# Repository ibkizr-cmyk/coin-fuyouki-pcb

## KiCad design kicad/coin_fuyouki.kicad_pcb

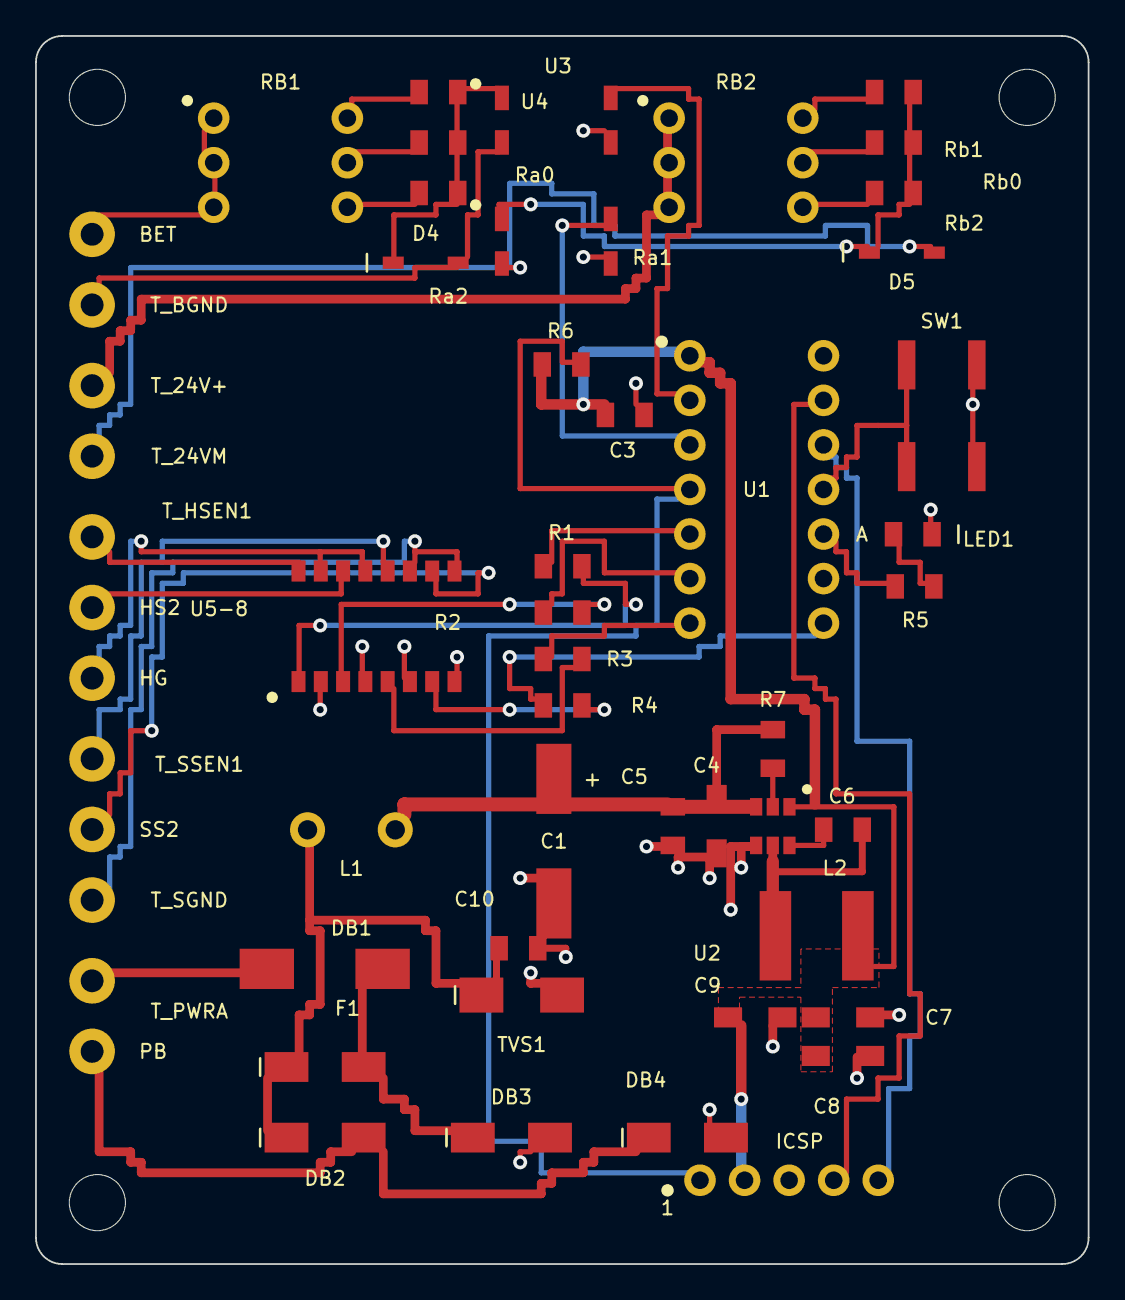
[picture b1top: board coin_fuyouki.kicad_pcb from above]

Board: 2 copper layers, 60.0 x 70.0 mm, 58 parts (0 on the bottom side), 44 nets.

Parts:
C1: EEE-FK1V101P; C1_custom
C3: 0.1uF; C3_custom
C4: 10uF/50V; C4_custom
C5: 0.1uF/50V; C5_custom
C6: 0.1uF; C6_custom
C7: 22uF/25V; C7_custom
C8: 22uF/25V; C8_custom
C9: 22uF/25V; C9_custom
C10: 0.1uF; C10_custom
D4: 1N4148W; D4_custom
D5: 1N4148W; D5_custom
DB1: SS16; DB1_custom
DB2: SS16; DB2_custom
DB3: SS16; DB3_custom
DB4: SS16; DB4_custom
F1: MF-SM050-2; F1_custom
H1, H2, H3, H4: M3; MountingHole_3.2mm
ICSP: 5P; ICSP_custom
L1: 100uH; L1_custom
L2: SRN6045TA-6R8M; L2_custom
LED1: LED; LED1_custom
R1: 470; R1_custom
R2: 470; R2_custom
R3: 470; R3_custom
R4: 470; R4_custom
R5: 1k; R5_custom
R6: 10k; R6_custom
R7: 100k; R7_custom
RB1: DIP3; RB1_custom
RB2: DIP3; RB2_custom
Ra0: 820; Ra0_custom
Ra1: 2.2k; Ra1_custom
Ra2: 4.7k; Ra2_custom
Rb0: 820; Rb0_custom
Rb1: 2.2k; Rb1_custom
Rb2: 4.7k; Rb2_custom
SW1: TACT; SW1_custom
TVS1: SMBJ26A; TVS1_custom
T_24V+: T_24V+_custom
T_24VM: T_24VM_custom
T_BET: T_BET_custom
T_BGND: T_BGND_custom
T_HGND: T_HGND_custom
T_HSEN1: T_HSEN1_custom
T_HSEN2: T_HSEN2_custom
T_PWRA: T_PWRA_custom
T_PWRB: T_PWRB_custom
T_SGND: T_SGND_custom
T_SSEN1: T_SSEN1_custom
T_SSEN2: T_SSEN2_custom
U1: PIC16F1503-I/P; U1_custom
U2: AP63205; U2_custom
U3: PC817; U3_custom
U4: PC817; U4_custom
U5-8: TLP291-4; U5-8_custom

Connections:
BA: D4.1, Ra0.2, Ra1.2, Ra2.2, U3.1
BET: RB1.1, RB1.2, RB1.3, T_BET.1
BETIN: U1.2, U3.4
BGND: D4.2, T_BGND.1, U3.2
BST: C6.1, U2.6
D1_a: R1.1, U1.5
D1_b: R1.2, U5-8.1
D2_a: R2.1, U1.6
D2_b: R2.2, U5-8.3
D3_a: R3.1, U1.7
D3_b: R3.2, U5-8.5
D4_a: R4.1, U1.8
D4_b: R4.2, U5-8.7
EN: R7.2, U2.2
GND: C1.2, C3.2, C4.2, C5.2, C7.2, C8.2, C9.2, C10.2, DB3.2, DB4.2, ICSP.3, LED1.2, SW1.2, TVS1.2, U1.14, U2.4, U3.3, U4.3, U5-8.2, U5-8.4, U5-8.6, U5-8.8
HA: D5.1, Rb0.2, Rb1.2, Rb2.2, U4.1
HGND: T_HGND.1, U5-8.13, U5-8.15
HOPIN: U1.3, U4.4
HSEN1: T_HSEN1.1, U5-8.16
HSEN2: T_HSEN2.1, U5-8.14
LEDa: LED1.1, R5.2
LEDd: R5.1, U1.10
MCLR: ICSP.1, R6.2, U1.4
MODE: SW1.1, U1.11
N24M: D5.2, T_24VM.1, U4.2
N24P: RB2.1, RB2.2, RB2.3, T_24V+.1
ND1: C10.1, DB1.1, DB2.1, L1.1, TVS1.1
NF: DB1.2, DB3.1, F1.2
NL: C1.1, C4.1, C5.1, L1.2, R7.1, U2.3
PGC: ICSP.5, U1.12
PGD: ICSP.4, U1.13
PWRA: F1.1, T_PWRA.1
PWRB: DB2.2, DB4.1, T_PWRB.1
RB1a: RB1.6, Ra0.1
RB1b: RB1.5, Ra1.1
RB1c: RB1.4, Ra2.1
RB2a: RB2.6, Rb0.1
RB2b: RB2.5, Rb1.1
RB2c: RB2.4, Rb2.1
SGND: T_SGND.1, U5-8.9, U5-8.11
SSEN1: T_SSEN1.1, U5-8.12
SSEN2: T_SSEN2.1, U5-8.10
SW: C6.2, L2.1, U2.5
V5: C3.1, C7.1, C8.1, C9.1, ICSP.2, L2.2, R6.1, U1.1, U2.1
